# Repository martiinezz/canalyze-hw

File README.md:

# CANalyze Hardware
Hardware for a CAN to USB device. This hardware can be used with the CANalyze
[firmware](https://github.com/kkuchera/canalyze-fw).

## Features
- USB type B and CAN DB9 connectors
- Supports both CiA DS102-2 and OBD2 type DB9 output via DIP switches
- Power via USB
- Red and green LED indicator
- This version is based on easier to handsolder SMD 0805

## TODO:
- Even smaller version without DIP switch
- MicroUSB connector
- No DB9 for CAN - just screw terminal to make PCB even smaller and easier to embed into the car permanently if needed

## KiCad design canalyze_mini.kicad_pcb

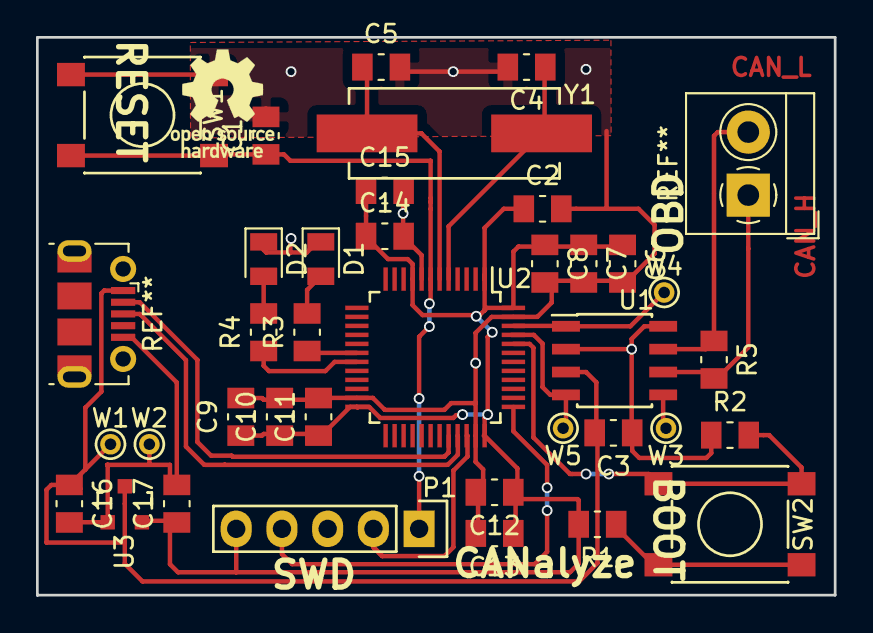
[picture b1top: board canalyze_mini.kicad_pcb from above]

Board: 2 copper layers, 44.3 x 31.0 mm, 36 parts (0 on the bottom side), 19 nets.

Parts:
C1, C2, C3, C7, C8, C10, C11, C12: 0.1u; C_0805_2012Metric_Pad1.15x1.50mm_HandSolder
C4, C5: 18p; C_0805_2012Metric_Pad1.15x1.50mm_HandSolder
C6, C9, C13: 4.7u; C_0805_2012Metric_Pad1.15x1.50mm_HandSolder
C14: 0.01u; C_0805_2012Metric_Pad1.15x1.50mm_HandSolder
C15, C16, C17: 1u; C_0805_2012Metric_Pad1.15x1.50mm_HandSolder
D1: LED_GREEN; LED_0805_2012Metric_Pad0.97x1.50mm_HandSolder
D2: LED_RED; LED_0805_2012Metric_Pad0.97x1.50mm_HandSolder
P1: SWD; Pin_Header_Straight_1x05
R1: 510; R_0805_2012Metric_Pad1.15x1.50mm_HandSolder
R2: 10k; R_0805_2012Metric_Pad1.15x1.50mm_HandSolder
R3, R4, R5: 120; R_0805_2012Metric_Pad1.15x1.50mm_HandSolder
SW1, SW2: SW_PUSH; SW_SPST_PTS645
U1: MCP2551-I/SN; SOIC-8_3.9x4.9mm_Pitch1.27mm
U2: STM32F042C6Tx; LQFP-48_7x7mm_Pitch0.5mm
U3: MCP1700T-3002E/TT; SOT-23
W1, W2, W3, W4, W5: TEST_1P; PINTST
Y1: Crystal; Crystal_HC49-SD_SMD

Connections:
+3V3: C2.1, C6.1, C7.1, C8.1, C9.1, C10.1, C11.1, C12.1, C13.1, C14.1, C15.1, C17.1, P1.5, R1.2, U2.1, U2.9, U2.24, U2.36, U2.48, U3.2
+5V: C3.2, C16.1, U1.3, U3.3, W1.1
/CAN_H: R5.1, U1.7
/CAN_L: R5.2, U1.6
/CAN_RX: U1.4, U2.45, W5.1
/CAN_TX: U1.1, U2.46, W4.1
/NRST: C1.1, P1.1, SW1.2, U2.7
/SWCLK: P1.4, U2.37
/SWDIO: P1.2, U2.34
/VREF: U1.5, W3.1
GND: C1.2, C2.2, C3.1, C4.2, C5.2, C6.2, C7.2, C8.2, C9.2, C10.2, C11.2, C12.2, C13.2, C14.2, C15.2, C16.2, C17.2, D1.1, D2.1, P1.3, R2.1, SW1.1, U1.2, U1.8, U2.8, U2.23, U2.35, U2.47, U3.1, W2.1
unnamed: C4.1, U2.5, Y1.1
unnamed: C5.1, U2.6, Y1.2
unnamed: D1.2, R3.2
unnamed: D2.2, R4.2
unnamed: R1.1, SW2.1
unnamed: R2.2, SW2.2, U2.44
unnamed: R3.1, U2.18
unnamed: R4.1, U2.19

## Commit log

2018-09-14 Update to SMD 0805, changed README with TODO
2018-09-14 TODOi changes
2018-09-14 Initial mini version
